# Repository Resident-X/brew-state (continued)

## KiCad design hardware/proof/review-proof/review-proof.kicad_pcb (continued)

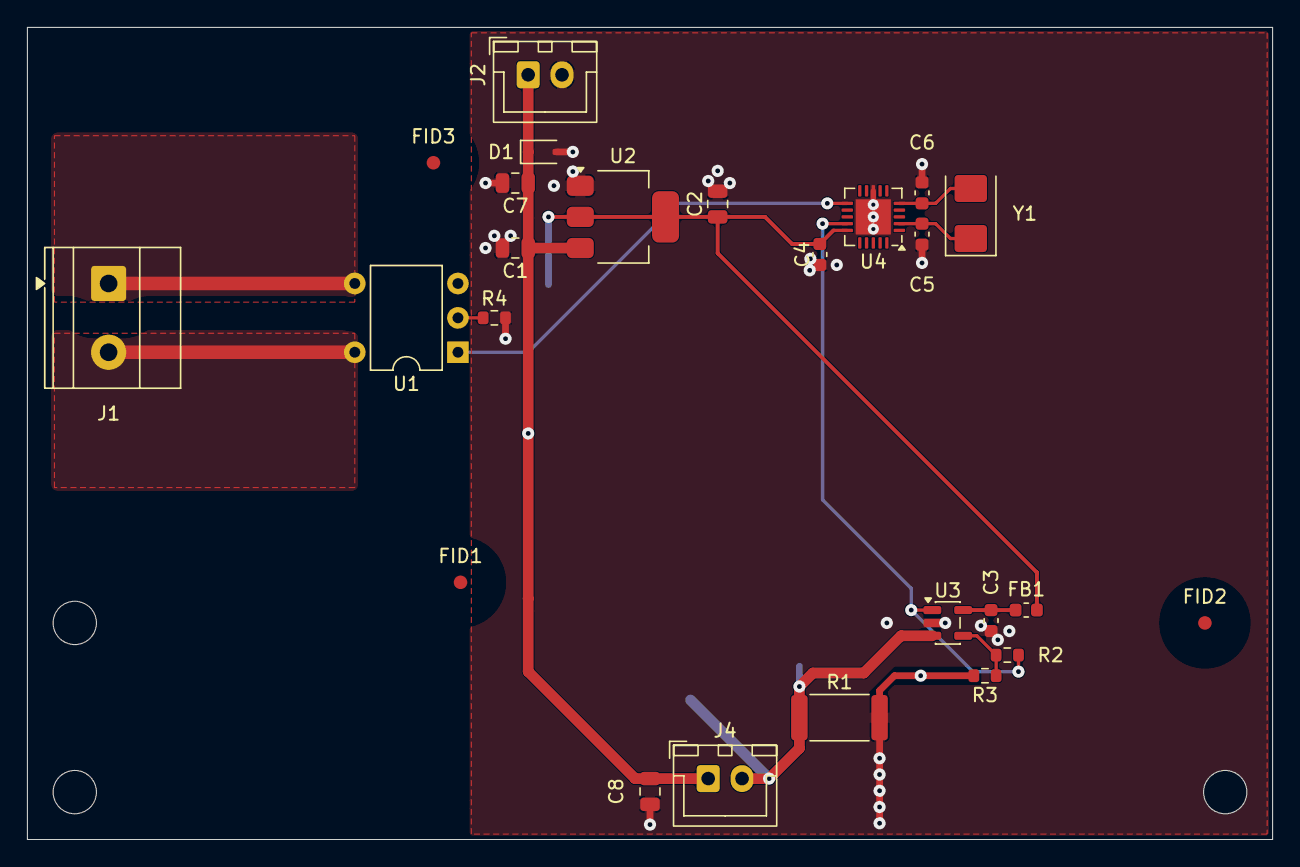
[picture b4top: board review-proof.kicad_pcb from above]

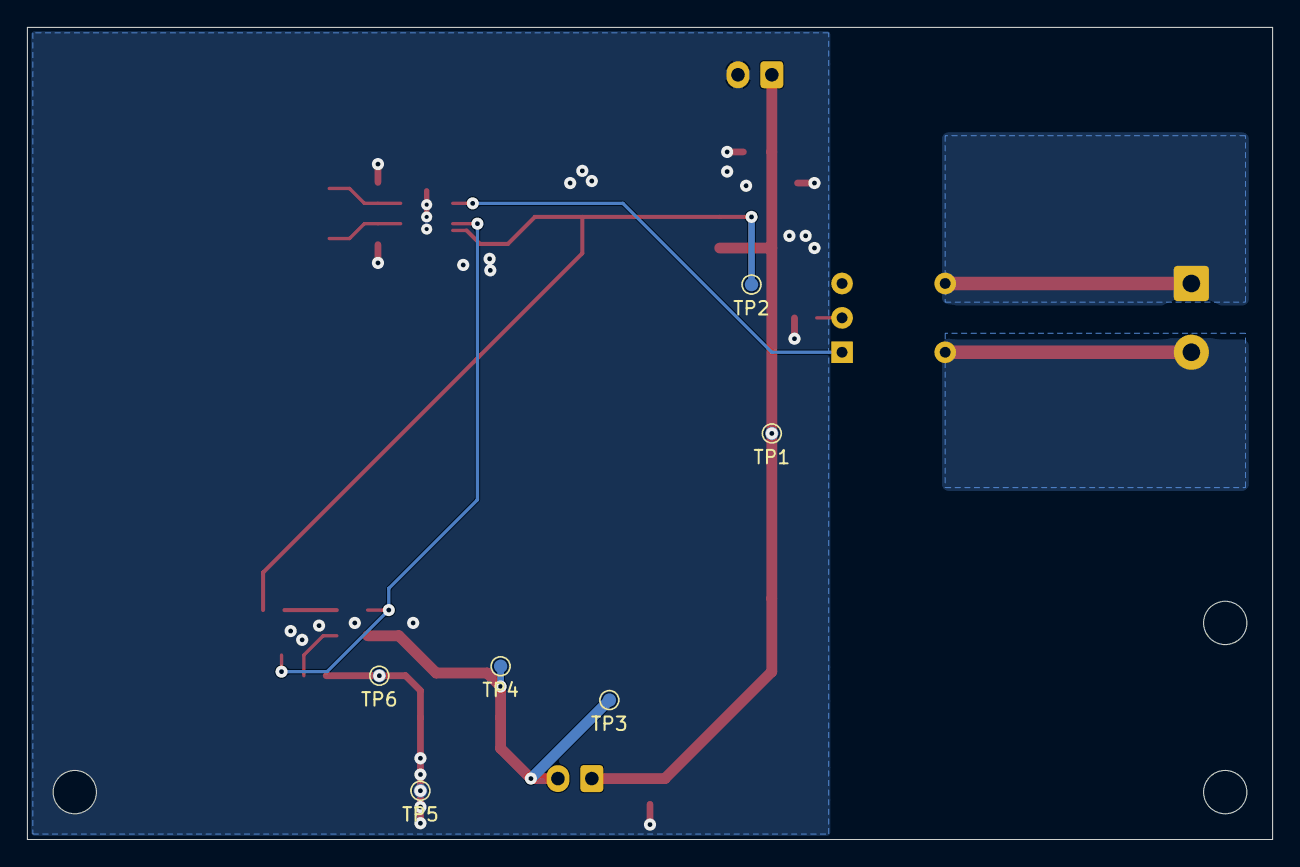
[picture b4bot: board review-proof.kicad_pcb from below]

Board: 4 copper layers, 92.0 x 60.0 mm, 34 parts (6 on the bottom side), 13 nets.

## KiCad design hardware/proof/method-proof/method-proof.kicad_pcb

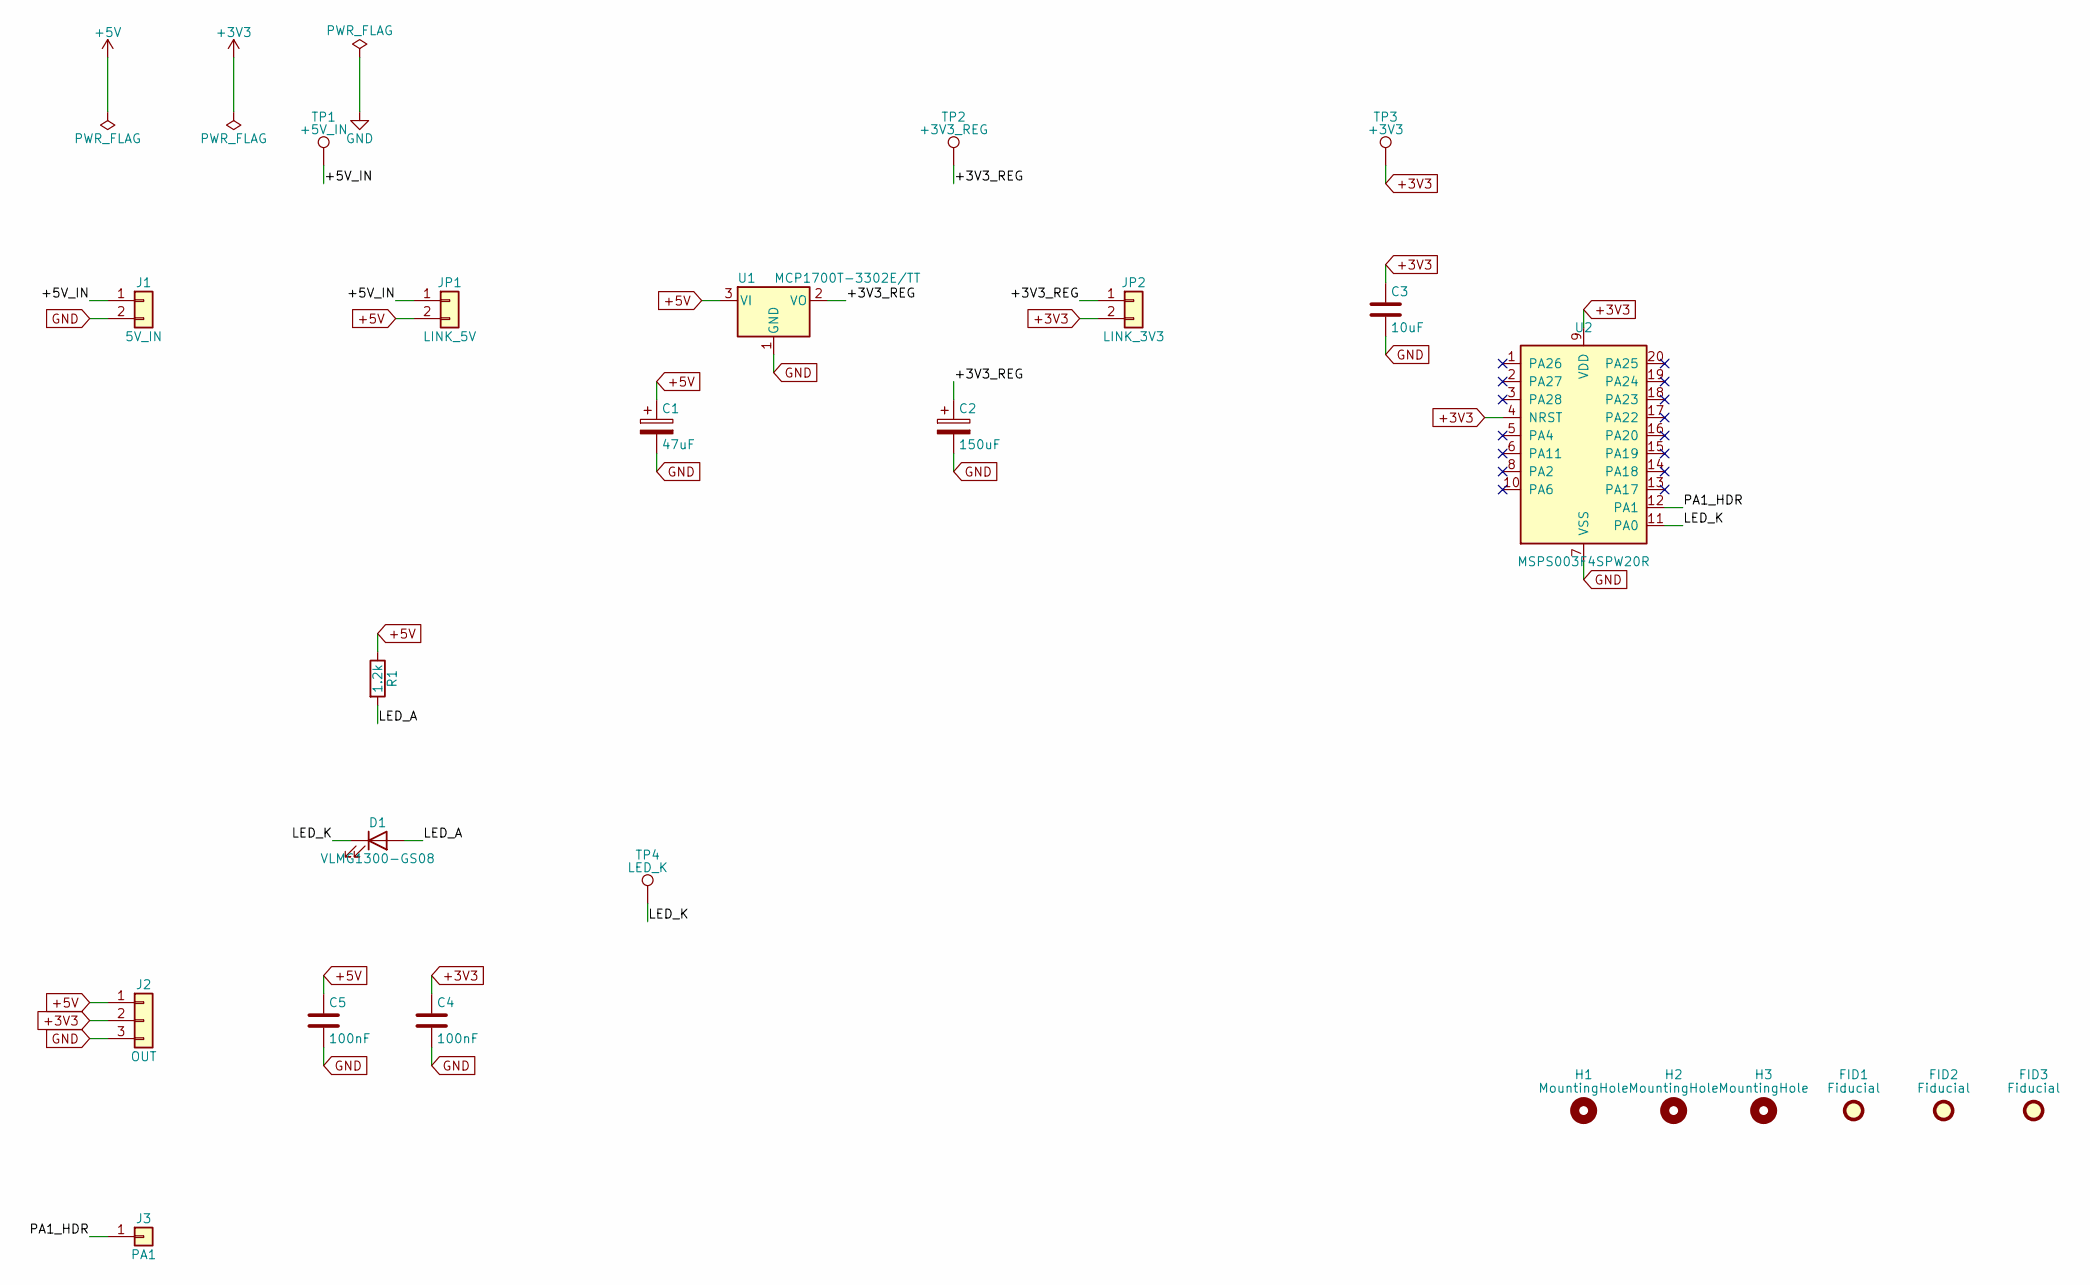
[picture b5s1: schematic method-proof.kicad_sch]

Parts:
C1: 47uF; CP_EIA-3528-21_Kemet-B; Rating 10V; MPN T520B476M010ATE035; LCSC C9100008
C2: 150uF; CP_EIA-3528-21_Kemet-B; Rating 6.3V; MPN T520B157M006ATE025; LCSC C9100014
C3: 10uF; C_0805_2012Metric; Rating 10V; MPN C0805C106K8RACTU; LCSC C9100009
C4, C5: 100nF; C_0603_1608Metric; Rating 16V; MPN C0603C104K4RACTU; LCSC C9100015
D1: VLMG1300-GS08; LED_0603_1608Metric; MPN VLMG1300-GS08; LCSC C9100011
FID1, FID2, FID3: Fiducial; Fiducial_1mm_Mask2mm; LCSC C9100016
H1, H2, H3: MountingHole; MountingHole_2.2mm_M2; LCSC C9100013
J1: 5V_IN; JST_XH_B2B-XH-A_1x02_P2.50mm_Vertical; Rating 3A; MPN B2B-XH-A(LF)(SN); LCSC C9100001
J2: OUT; JST_XH_B3B-XH-A_1x03_P2.50mm_Vertical; Rating 3A; MPN B3B-XH-A(LF)(SN); LCSC C9100002
J3: PA1; PinHeader_1x01_P2.54mm_Vertical; MPN TSW-101-07-T-S; LCSC C9100003
JP1: LINK_5V; PinHeader_1x02_P2.54mm_Vertical; MPN TSW-102-07-T-S; LCSC C9100004
JP2: LINK_3V3; PinHeader_1x02_P2.54mm_Vertical; MPN TSW-102-07-T-S; LCSC C9100005
R1: 1.2k; R_0603_1608Metric; Rating 0.1W; MPN CRCW06031K20FKEA; LCSC C9100010
TP1: +5V_IN; TestPoint_Pad_D1.0mm; LCSC C9100012
TP2: +3V3_REG; TestPoint_Pad_D1.0mm; LCSC C9100012
TP3: +3V3; TestPoint_Pad_D1.0mm; LCSC C9100012
TP4: LED_K; TestPoint_Pad_D1.0mm; LCSC C9100012
U1: MCP1700T-3302E/TT; SOT-23; MPN MCP1700T-3302E/TT; LCSC C9100006
U2: MSPS003F4SPW20R; TSSOP-20_4.4x6.5mm_P0.65mm; MPN MSPS003F4SPW20R; LCSC C9100007

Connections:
+3V3: C3.1, C4.1, J2.2, JP2.2, TP3.1 (1_1), U2.4 (NRST), U2.9 (VDD)
+5V: C1.1, C5.1, J2.1, JP1.2, R1.1, U1.3 (VI)
/+3V3_REG: C2.1, JP2.1, TP2.1 (1_1), U1.2 (VO)
/+5V_IN: J1.1, JP1.1, TP1.1 (1_1)
/LED_A: D1.2 (A), R1.2
/LED_K: D1.1 (K), TP4.1 (1_1), U2.11 (PA0)
/PA1_HDR: J3.1 (Pin_1_1), U2.12 (PA1)
GND: C1.2, C2.2, C3.2, C4.2, C5.2, J1.2, J2.3, U1.1 (GND), U2.7 (VSS)

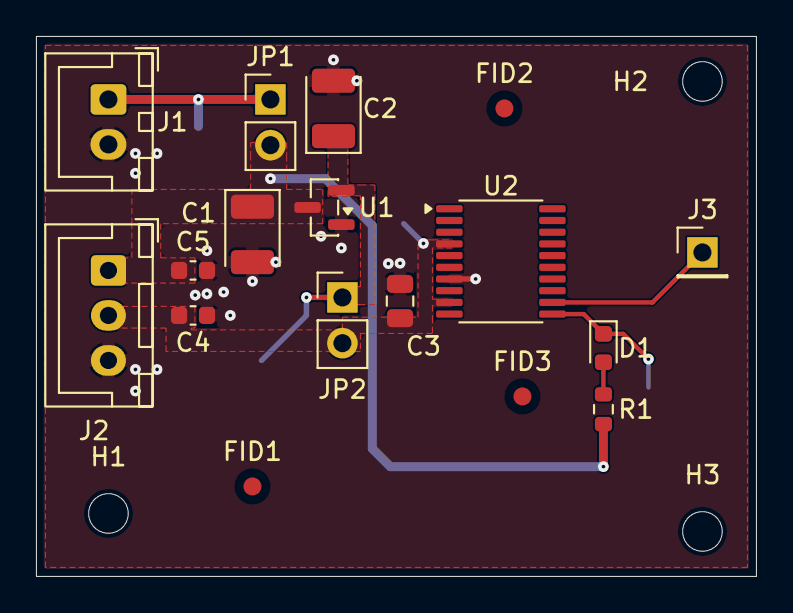
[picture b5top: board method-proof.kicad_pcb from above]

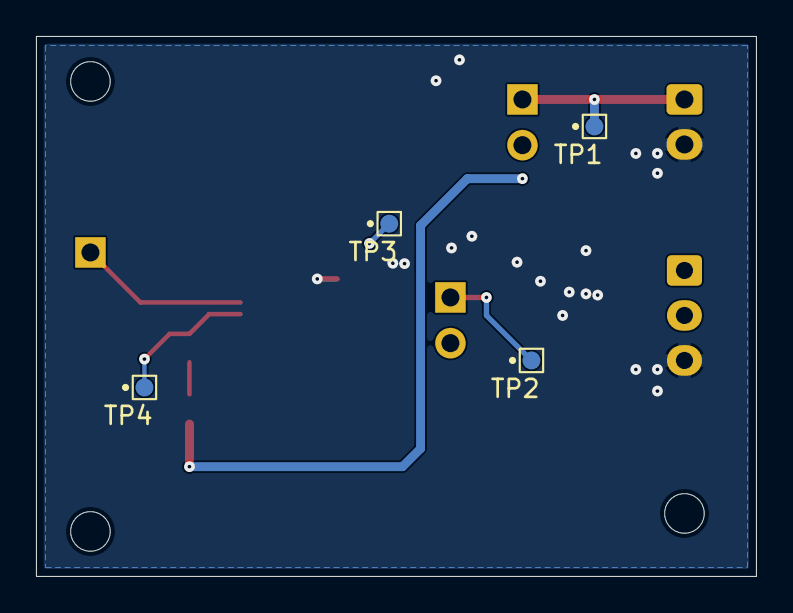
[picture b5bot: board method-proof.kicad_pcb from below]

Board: 4 copper layers, 40.0 x 30.0 mm, 24 parts (4 on the bottom side), 8 nets.
